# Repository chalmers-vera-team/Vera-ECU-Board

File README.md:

# Vera-ECU-Board
A PCB to break out connections to a MicroSquirt Engine Control Unit. Meant to be implemented for the Vera car of Chalmers Vera Team.
PCBWay sponsored the PCB and you can read about it [here!](http://chalmersverateam.se/wp-content/uploads/2019/12/PCBWAY_2019.pdf)

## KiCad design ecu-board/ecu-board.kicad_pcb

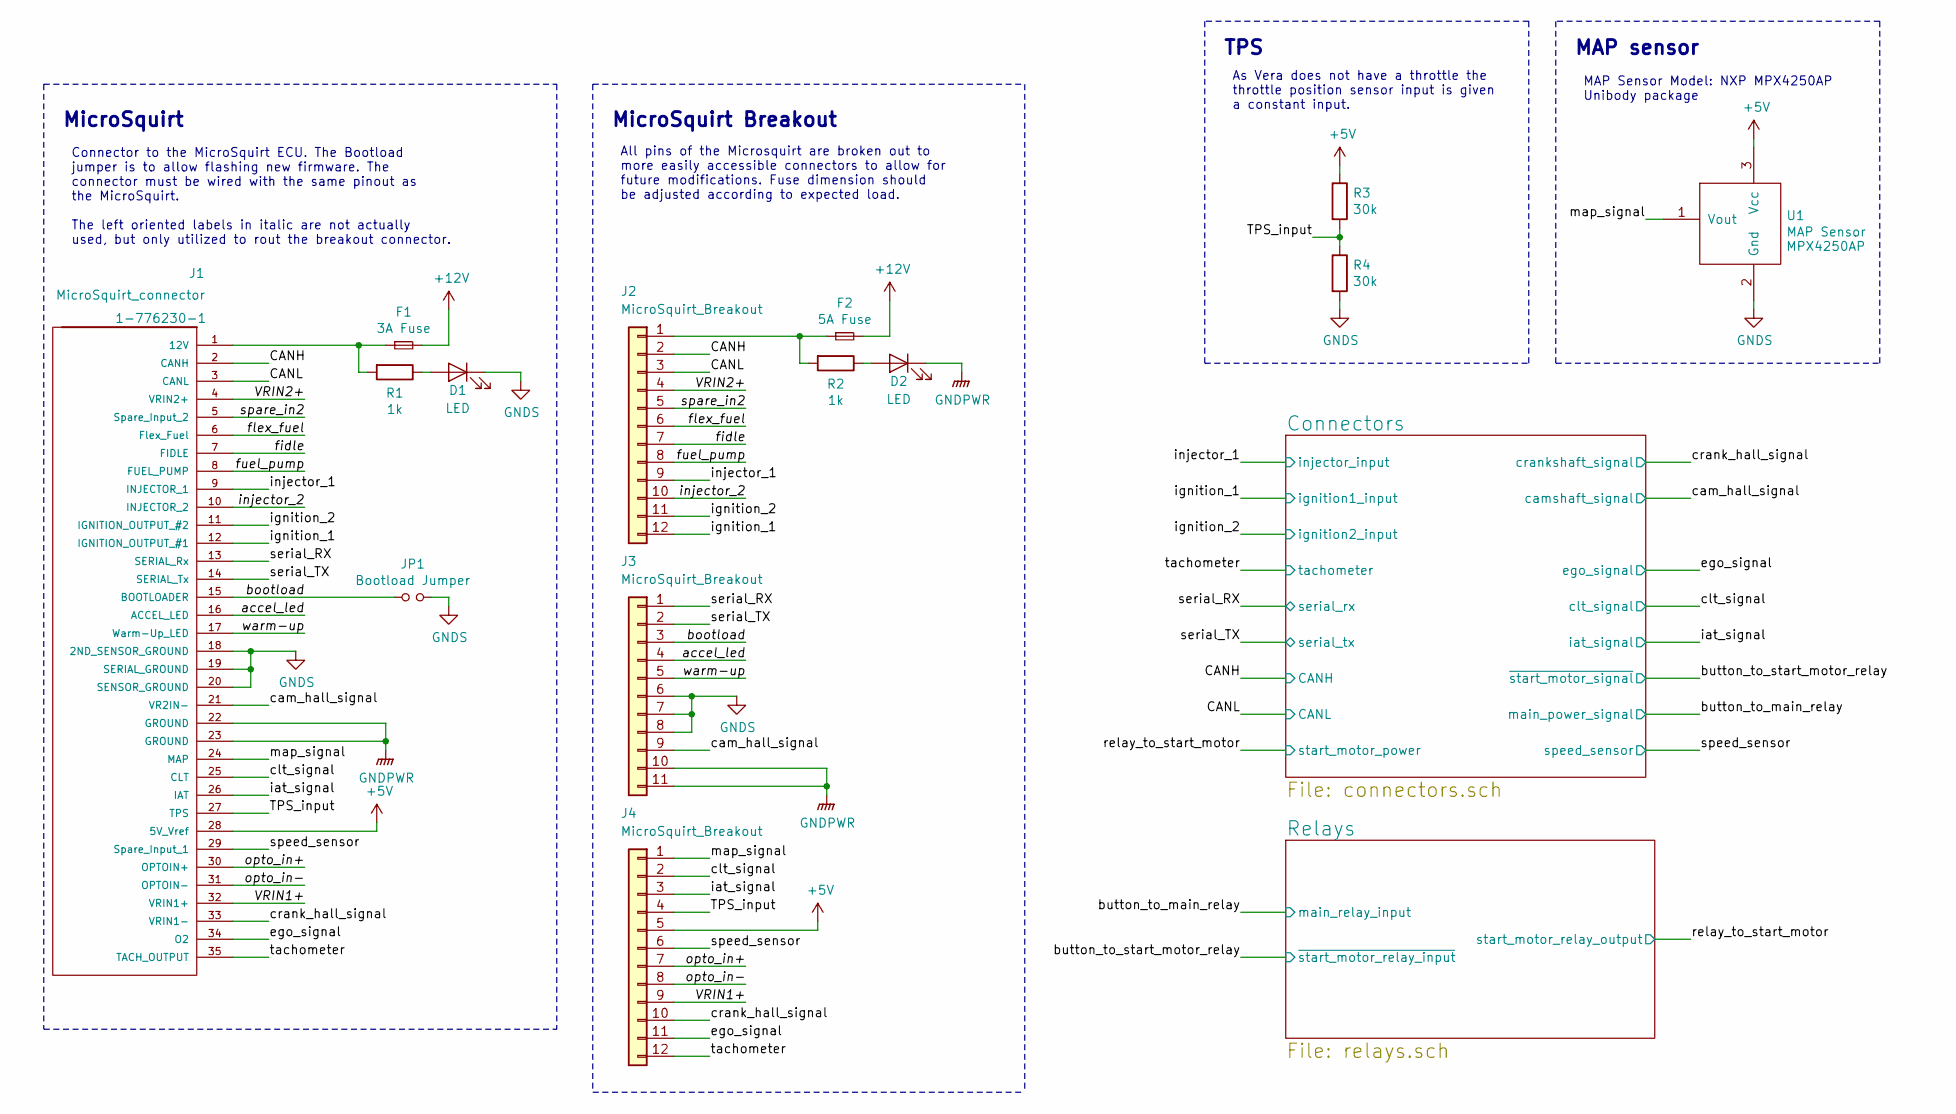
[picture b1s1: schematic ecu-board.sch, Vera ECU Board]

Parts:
D1, D2: LED; LED_0805_HandSoldering; Part no. 0805
F1: 3A Fuse; Fuseholder_ATO_Blade_Littelfuse_Pudenz_4_Pin; Part no. 178.4265.0002
F2: 5A Fuse; Fuseholder_ATO_Blade_Littelfuse_Pudenz_4_Pin; Part no. 178.4265.0002
J1: MicroSquirt_connector; TE_1-776230-1_35POS_P4.0mm_Vertical; Part no. 1-776230-1
J2, J4: MicroSquirt_Breakout; PinHeader_1x12_P2.54mm_Vertical; Part no. 2.54mm Pin Header
J3: MicroSquirt_Breakout; PinHeader_1x11_P2.54mm_Vertical; Part no. 2.54mm Pin Header
JP1: Bootload Jumper; Pin_Header_Straight_1x02_Pitch2.54mm; Part no. 2.54mm Pin Header
R1, R2: 1k; R_0805_HandSoldering; Part no. 0805
R3, R4: 30k; R_0805_HandSoldering; Part no. 0805
U1: MAP Sensor; SOT1852-1; Part no. MPX4250AP

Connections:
+5V: J1.28 (5V_Vref), J4.5, R3.1, U1.3 (Vcc)
+12V: F1.2, F2.2; also elsewhere on the board
/CANH: J1.2 (CANH), J2.2; also elsewhere on the board
/CANL: J1.3 (CANL), J2.3; also elsewhere on the board
/TPS_input: J1.27 (TPS), J4.4, R3.2, R4.1
/VRIN1+: J1.32 (VRIN1+), J4.9
/VRIN2+: J1.4 (VRIN2+), J2.4
/accel_led: J1.16 (ACCEL_LED), J3.4
/bootload: J1.15 (BOOTLOADER), J3.3, JP1.1
/cam_hall_signal: J1.21 (VR2IN-), J3.9; also elsewhere on the board
/clt_signal: J1.25 (CLT), J4.2; also elsewhere on the board
/crank_hall_signal: J1.33 (VRIN1-), J4.10; also elsewhere on the board
/ego_signal: J1.34 (O2), J4.11; also elsewhere on the board
/fidle: J1.7 (FIDLE), J2.7
/flex_fuel: J1.6 (Flex_Fuel), J2.6
/fuel_pump: J1.8 (FUEL_PUMP), J2.8
/iat_signal: J1.26 (IAT), J4.3; also elsewhere on the board
/ignition_1: J1.12 (IGNITION_OUTPUT_#1), J2.12; also elsewhere on the board
/ignition_2: J1.11 (IGNITION_OUTPUT_#2), J2.11; also elsewhere on the board
/injector_1: J1.9 (INJECTOR_1), J2.9; also elsewhere on the board
/injector_2: J1.10 (INJECTOR_2), J2.10
/map_signal: J1.24 (MAP), J4.1, U1.1 (Vout)
/opto_in+: J1.30 (OPTOIN+), J4.7
/opto_in-: J1.31 (OPTOIN-), J4.8
/serial_RX: J1.13 (SERIAL_Rx), J3.1; also elsewhere on the board
/serial_TX: J1.14 (SERIAL_Tx), J3.2; also elsewhere on the board
/spare_in2: J1.5 (Spare_Input_2), J2.5
/speed_sensor: J1.29 (Spare_Input_1), J4.6; also elsewhere on the board
/tachometer: J1.35 (TACH_OUTPUT), J4.12; also elsewhere on the board
/warm-up: J1.17 (Warm-Up_LED), J3.5
GNDPWR: D2.1 (K), J1.22 (GROUND), J1.23 (GROUND), J3.10, J3.11; also elsewhere on the board
GNDS: D1.1 (K), J1.18 (2ND_SENSOR_GROUND), J1.19 (SERIAL_GROUND), J1.20 (SENSOR_GROUND), J3.6, J3.7, J3.8, JP1.2, R4.2, U1.2 (Gnd); also elsewhere on the board
unnamed: D1.2 (A), R1.1
unnamed: D2.2 (A), R2.1
unnamed: F1.1, J1.1 (12V), R1.2
unnamed: F2.1, J2.1, R2.2

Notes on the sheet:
MicroSquirt
Connector to the MicroSquirt ECU. The Bootload jumper is to allow flashing new firmware. The connector must be wired with the same pinout as the MicroSquirt. The left oriented labels in italic are not actually used, but only utilized to rout the breakout connector.
MAP sensor
MAP Sensor Model: NXP MPX4250AP Unibody package
TPS
As Vera does not have a throttle the throttle position sensor input is given a constant input.
MicroSquirt Breakout
All pins of the Microsquirt are broken out to more easily accessible connectors to allow for future modifications. Fuse dimension should be adjusted according to expected load.

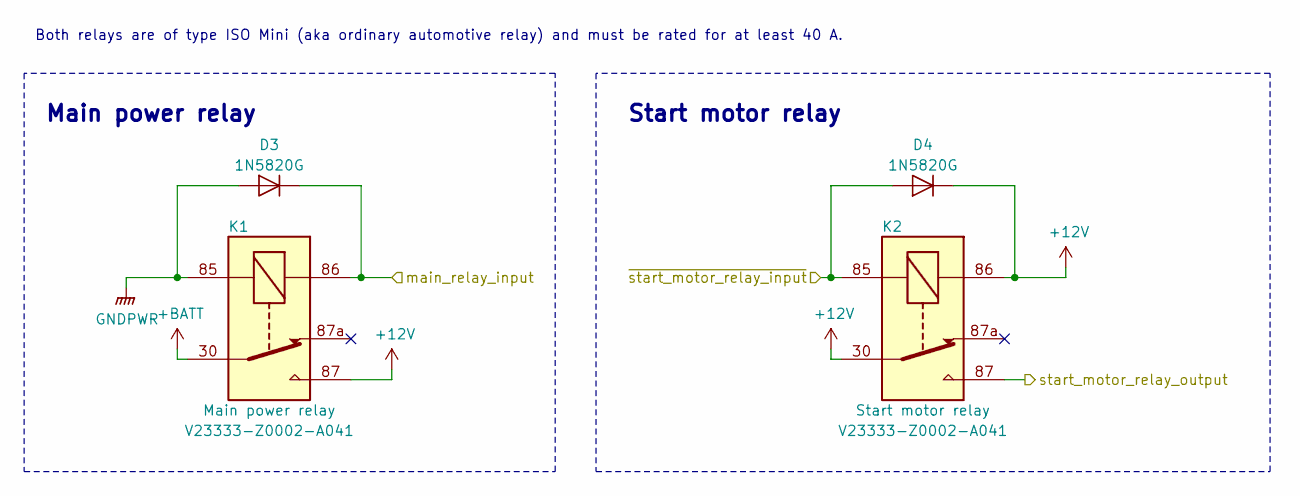
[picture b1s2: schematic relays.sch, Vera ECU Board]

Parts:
D3, D4: 1N5820G; D_DO-201AD_P15.24mm_Horizontal; Part no. 1N5820G
K1: Main power relay; TE_2-1904045-4; Part no. V23333-Z0002-A041
K2: Start motor relay; TE_2-1904045-4; Part no. V23333-Z0002-A041

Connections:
+12V: D4.1 (K), K1.87, K2.30, K2.86; also elsewhere on the board
+BATT: K1.30; also elsewhere on the board
/button_to_main_relay: D3.1 (K), K1.86; also elsewhere on the board
/button_to_start_motor_relay: D4.2 (A), K2.85; also elsewhere on the board
/relay_to_start_motor: K2.87; also elsewhere on the board
GNDPWR: D3.2 (A), K1.85; also elsewhere on the board

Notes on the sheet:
Main power relay
Start motor relay
Both relays are of type ISO Mini (aka ordinary automotive relay) and must be rated for at least 40 A.

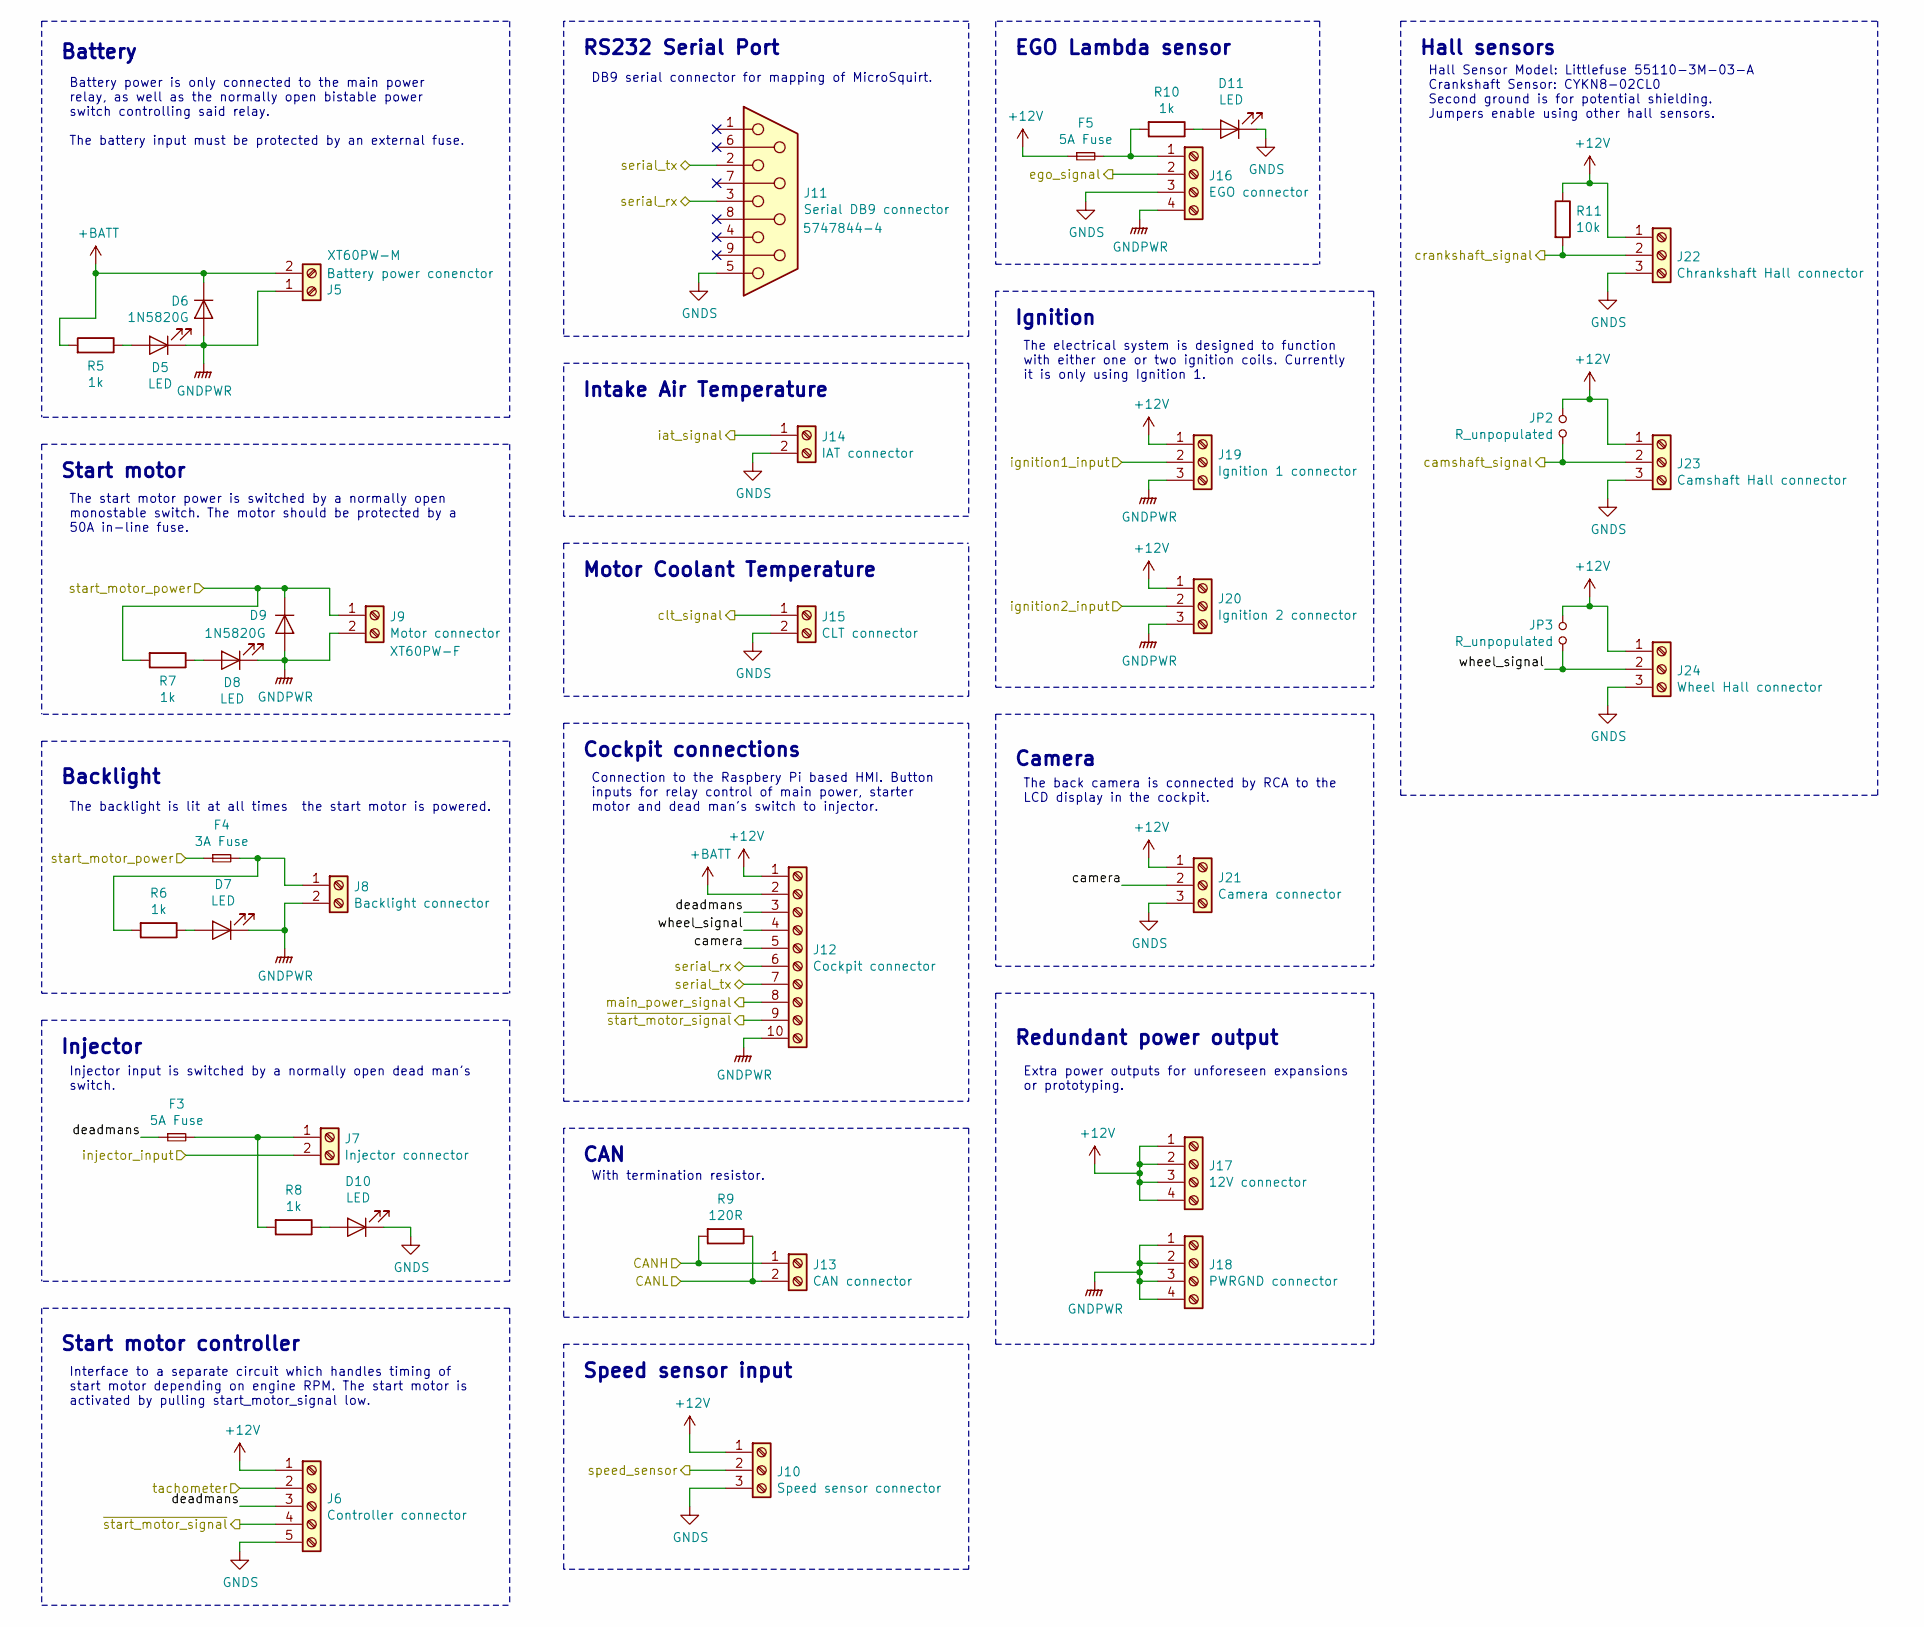
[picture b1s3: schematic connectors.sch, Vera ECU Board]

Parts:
D5, D7, D8, D10, D11: LED; LED_0805_HandSoldering; Part no. 0805
D6, D9: 1N5820G; D_DO-201AD_P15.24mm_Horizontal; Part no. 1N5820G
F3, F5: 5A Fuse; Fuseholder_ATO_Blade_Littelfuse_Pudenz_4_Pin; Part no. 178.4265.0002
F4: 3A Fuse; Fuseholder_ATO_Blade_Littelfuse_Pudenz_4_Pin; Part no. 178.4265.0002
J5: Battery power conenctor; AMASS_XT60PW; Part no. XT60PW-M
J6: Controller connector; Terminal_Block_5x5.00mm; Part no. 897-0812
J7: Injector connector; Terminal_Block_2x5.00mm; Part no. 897-0803
J8: Backlight connector; Terminal_Block_2x5.00mm; Part no. 897-0803
J9: Motor connector; AMASS_XT60PW; Part no. XT60PW-F
J10: Speed sensor connector; Terminal_Block_3x5.00mm; Part no. 897-0812
J11: Serial DB9 connector; TE_5747844-4; Part no. 5747844-4
J12: Cockpit connector; Terminal_Block_10x5.00mm; Part no. 897-0803
J13: CAN connector; Terminal_Block_2x5.00mm; Part no. 897-0803
J14: IAT connector; Terminal_Block_2x5.00mm; Part no. 897-0803
J15: CLT connector; Terminal_Block_2x5.00mm; Part no. 897-0803
J16: EGO connector; Terminal_Block_4x5.00mm; Part no. 897-0803
J17: 12V connector; Terminal_Block_4x5.00mm; Part no. 897-0803
J18: PWRGND connector; Terminal_Block_4x5.00mm; Part no. 897-0803
J19: Ignition 1 connector; Terminal_Block_3x5.00mm; Part no. 897-0812
J20: Ignition 2 connector; Terminal_Block_3x5.00mm; Part no. 897-0812
J21: Camera connector; Terminal_Block_3x5.00mm; Part no. 897-0812
J22: Chrankshaft Hall connector; Terminal_Block_3x5.00mm; Part no. 897-0812
J23: Camshaft Hall connector; Terminal_Block_3x5.00mm; Part no. 897-0812
J24: Wheel Hall connector; Terminal_Block_3x5.00mm; Part no. 897-0812
JP2, JP3: R_unpopulated; R_0805_HandSoldering; Part no. 0805
R5, R6, R7, R8, R10: 1k; R_0805_HandSoldering; Part no. 0805
R9: 120R; R_0805_HandSoldering; Part no. 0805
R11: 10k; R_0805_HandSoldering; Part no. 0805

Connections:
+12V: F5.1, J6.1, J10.1, J12.1, J17.1, J17.2, J17.3, J17.4, J19.1, J20.1, J21.1, J22.1, J23.1, J24.1, JP2.2, JP3.2, R11.1; also elsewhere on the board
+BATT: D6.1 (K), J5.2, J12.2, R5.2; also elsewhere on the board
/CANH: J13.1, R9.2; also elsewhere on the board
/CANL: J13.2, R9.1; also elsewhere on the board
/Connectors/camera: J12.5, J21.2
/Connectors/deadmans: F3.1, J6.3, J12.3
/Connectors/wheel_signal: J12.4, J24.2, JP3.1
/button_to_main_relay: J12.8; also elsewhere on the board
/button_to_start_motor_relay: J6.4, J12.9; also elsewhere on the board
/cam_hall_signal: J23.2, JP2.1; also elsewhere on the board
/clt_signal: J15.1; also elsewhere on the board
/crank_hall_signal: J22.2, R11.2; also elsewhere on the board
/ego_signal: J16.2; also elsewhere on the board
/iat_signal: J14.1; also elsewhere on the board
/ignition_1: J19.2; also elsewhere on the board
/ignition_2: J20.2; also elsewhere on the board
/injector_1: J7.2; also elsewhere on the board
/relay_to_start_motor: D9.1 (K), F4.1, J9.1, R7.2; also elsewhere on the board
/serial_RX: J11.3, J12.6; also elsewhere on the board
/serial_TX: J11.2, J12.7; also elsewhere on the board
/speed_sensor: J10.2; also elsewhere on the board
/tachometer: J6.2; also elsewhere on the board
GNDPWR: D5.1 (K), D6.2 (A), D7.1 (K), D8.1 (K), D9.2 (A), J5.1, J8.2, J9.2, J12.10, J16.4, J18.1, J18.2, J18.3, J18.4, J19.3, J20.3; also elsewhere on the board
GNDS: D10.1 (K), D11.1 (K), J6.5, J10.3, J11.5, J14.2, J15.2, J16.3, J21.3, J22.3, J23.3, J24.3; also elsewhere on the board
unnamed: D5.2 (A), R5.1
unnamed: D7.2 (A), R6.1
unnamed: D8.2 (A), R7.1
unnamed: D10.2 (A), R8.1
unnamed: D11.2 (A), R10.1
unnamed: F3.2, J7.1, R8.2
unnamed: F4.2, J8.1, R6.2
unnamed: F5.2, J16.1, R10.2

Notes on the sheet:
Hall Sensor Model: Littlefuse 55110-3M-03-A Crankshaft Sensor: CYKN8-02CL0 Second ground is for potential shielding. Jumpers enable using other hall sensors.
Hall sensors
EGO Lambda sensor
RS232 Serial Port
DB9 serial connector for mapping of MicroSquirt.
Injector
Injector input is switched by a normally open dead man's switch.
Motor Coolant Temperature
Intake Air Temperature
Battery
Start motor
The start motor power is switched by a normally open monostable switch. The motor should be protected by a 50A in-line fuse.
Ignition
The electrical system is designed to function with either one or two ignition coils. Currently it is only using Ignition 1.
Cockpit connections
Connection to the Raspbery Pi based HMI. Button inputs for relay control of main power, starter motor and dead man's switch to injector.
Start motor controller
Interface to a separate circuit which handles timing of start motor depending on engine RPM. The start motor is activated by pulling start_motor_signal low.
Camera
The back camera is connected by RCA to the LCD display in the cockpit.
Backlight
The backlight is lit at all times the start motor is powered.
Battery power is only connected to the main power relay, as well as the normally open bistable power switch controlling said relay. The battery input must be protected by an external fuse.
CAN
Speed sensor input
With termination resistor.
Redundant power output
Extra power outputs for unforeseen expansions or prototyping.

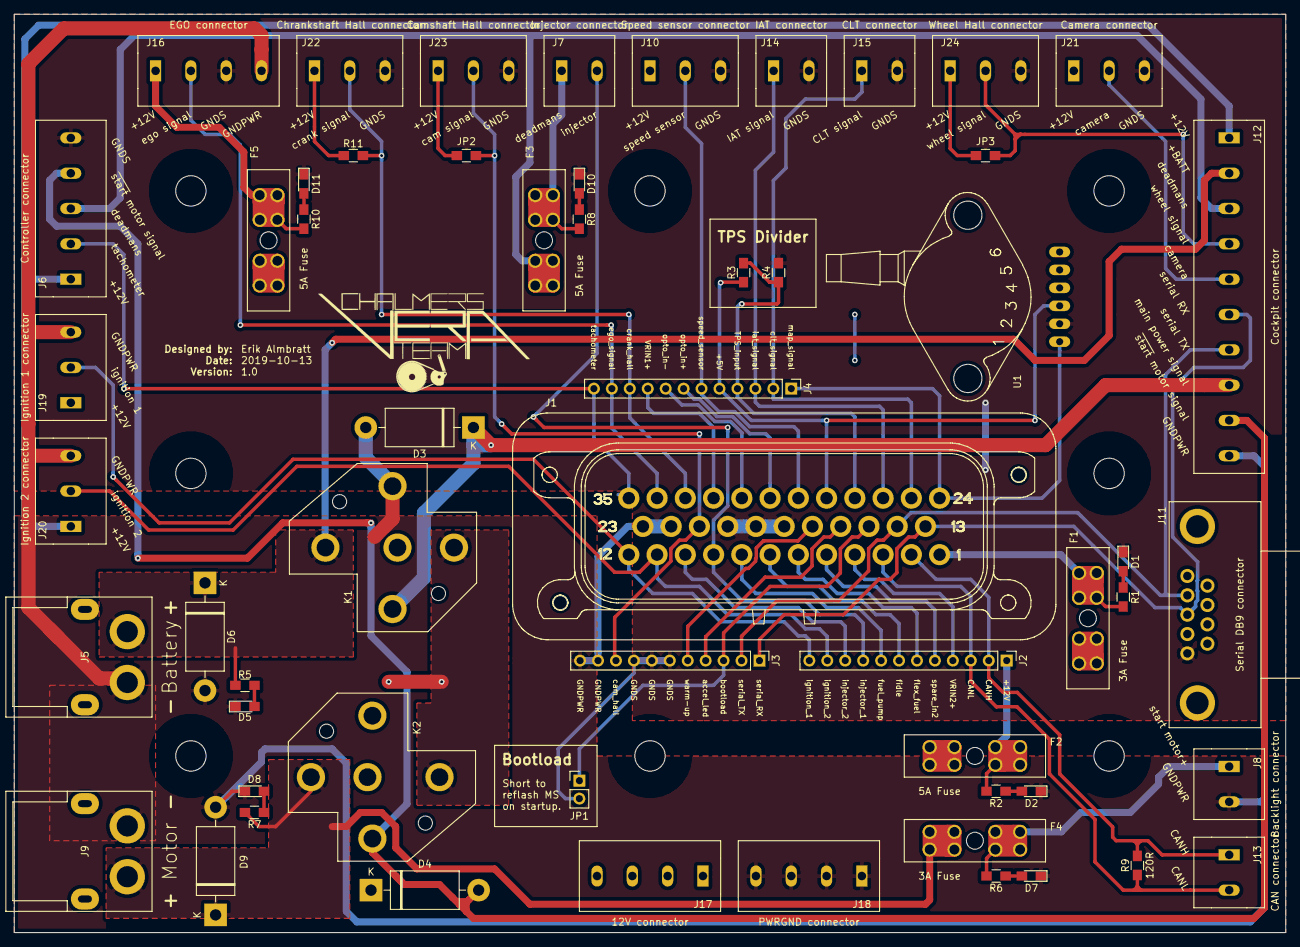
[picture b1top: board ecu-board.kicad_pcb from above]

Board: 2 copper layers, 180.0 x 130.0 mm, 57 parts (0 on the bottom side), 51 nets.

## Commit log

2019-02-03 Hall and MAP sensor connectors created.
2019-02-04 Schematic completed. Now to confirm details and proof-read.
2019-02-04 README updated
2019-02-04 Readme updated again and old svg removed.
2019-02-10 Fixed typo in README.md
2019-02-24 Add gitignore.
2019-02-24 Add Power Ground to lambda connector
2019-02-24 Remove relay pull downs.
2019-02-24 Update crankshaft sensor model.
2019-02-24 Mount MAP sensor to PCB. Reverse injector input.
2019-02-24 Cockpit connector expanded and merged with button connector. Injector connected to dead man's switch.
2019-02-24 Schematics images updated.
2019-03-26 Change TPS. Resolved #27.
2019-03-26 Add pull up to Crankshaft hall. Resolves #16.
2019-03-26 Add pull up placeholders to hall sensors. Resolves #18
2019-03-26 Moved tachometer output and start motor controll to separate circuit. Resolves #20 and resolves #25.
2019-03-26 Added indicator LEDs to fuses. Resolves #15.
2019-03-29 Clean up schematic graphics.
2019-05-15 Specified diodes.
2019-05-15 Change start motor relay connection. To comply with the external start motor module. Solves #28.
2019-05-15 Update schematic pdf and svgs.
2019-05-16 Remove main fuse. To be replaced by inline. See #4.
2019-05-16 Add camera connector. #21.
2019-05-16 Add backlight connector. Resolves #21.
2019-05-16 Update schematics.
2019-07-02 Add fb-lib-table
2019-07-04 Change starter motor fuse to 40A. Closes #30.
2019-07-04 Remove unecessary pull-down.
2019-07-04 Change hal connectors from 4 to 3 pin.
2019-07-04 Add backlight fuse. Closes #31.
2019-07-06 Update SVGs
2019-07-06 Add info about start motor.
2019-07-07 Add MicroSquirt Breakout. Closes #10.
2019-07-07 Add footprint information.
2019-07-08 Add reverse polarity protection. Closes #35.
2019-07-08 Mirror MOSFET orientationgit status
2019-07-13 Add Wurth terminal block footprints.
2019-07-13 Assign 2- and 3-pin terminal footprints.
2019-07-14 Create 4x terminal footprint. Closes #41.
2019-07-14 Create 5x terminal footprint. Closes #40.
2019-07-14 Adjust footprint 3d model position.
2019-07-14 Create 10x terminal footprint. Closes #39.
2019-07-14 Assign block terminal footprints.
2019-07-14 Add component part no.
2019-07-14 Display power connector part no.
2019-07-14 Create 1-776230-1 footprint.
2019-08-06 Complete XT60PW footprint.
2019-08-06 Assign XT60PW footprints to symbols.
2019-08-06 Update mosfet data sheet.
2019-08-06 Add relay article information.
2019-08-06 Remove legacy Farnell article no.
2019-08-06 Update DB9 article information.
2019-08-06 Remove legacy datasheet.
2019-08-06 Add DB9 footprint.
2019-08-06 Remove start motor fuse due to too high current.
2019-08-06 Change diodes.
2019-08-06 Update LEDs.
2019-08-06 Update MAP sensor value.
2019-08-06 Update jumper info.
2019-08-06 Update fuse holder info.
2019-08-06 Assign resistor footprints.
2019-08-06 Assign diode footprints.
2019-08-06 Assign jumper footprint.
2019-08-12 Initial placement on components.
2019-08-16 Adjust Ampseal mounting hole size.
2019-08-16 Assign ampseal connector.
2019-08-16 Create relay footprint.
2019-08-16 Assign relay footprints.
2019-08-16 Adjust dsub-9 footprint.
2019-08-17 Add MPX4250AP footprint. Closes #46.
2019-08-17 Assign MAP footprint.
2019-08-17 Ignore backup files.
2019-08-17 Update dsub connector in pcb. Closes #42.
2019-08-17 Ignore lib cache files.
2019-08-17 Add part names to relay symbols.
2019-08-17 Add part values to connector symbols.
2019-08-17 Reassign footprints to 0805.
2019-08-17 Change from 3.50mm to 5.00mm terminal blocks.
2019-08-29 Change fuse part no.
2019-08-29 Add fuse holder footprint.
2019-08-29 Import fuse holders to pcb.
2019-08-29 Layout fuses.
2019-08-29 Add breakout connector.
2019-08-30 Make symbol import path relative to project.
2019-08-30 Rearrange some components on pcb.
2019-09-29 Change reverse polarity protection to diode.
2019-09-29 Rename board signals.
2019-09-29 Switch serial rx/tx.
2019-09-29 Add CAN connector.
2019-09-29 Add speed sensor connector.
2019-09-29 Add CAN termination resitor.
2019-09-29 Start power circuit routing.
2019-09-29 Route almost everything.
2019-10-04 Create isolated M4 footprint.
2019-10-04 Place mounting holes.
2019-10-04 Finish work session.
2019-10-12 Adjust dimension drawing.
2019-10-12 Change cockpit ground from SGND to PWRGND.
2019-10-12 Add redundant 12V and PWRGND connectors. Closes #52. Also add PWRGND copper pour.
2019-10-12 Correct BOM to present components.
2019-10-12 Split MicroSquirt breakout connector into three separate connectors. Old connector was impossible to route.
2019-10-12 Change block terminal article.
2019-10-12 Add connector pinout to silkscreen.
2019-10-12 Add lots of silk screen.
2019-10-12 Route full board.
2019-10-12 Clean up copper pours.
2019-10-12 Generate PDF and SVG files.
2019-10-12 Change to a larger diode footprint.
2019-10-12 Correct unconnected pad.
2019-10-13 Move relays and additional final touches.
2019-10-13 Update board svg.
2019-10-13 Update documentation images.
2019-10-13 Add step 3D model.
2019-10-13 Add png image.
2019-12-15 Added a sponsor
